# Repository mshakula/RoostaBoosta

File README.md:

# RoostaBoosta

Who doesn't need a good morning boost?
Return to your rich idyllic pastoral roots with RoostaBoosta™, the innovative, awesome, groundbreaking, fascinating, mind-boggling, stupendous IoT weather-predicting alarm clock!

Final project for Georgia Tech ECE4180.
Based on the newer [MbedOS 6](https://os.mbed.com/docs/mbed-os/v6.16/introduction/index.html) platform, this project incorporates networking, API calls, and audio-visual effects for an web-enabled alarm clock / weather prediction station.

## Building

Since the project is based on MbedOS 6, it strives to support the newer Mbed CLI 2, which among other things has [CMake support](https://os.mbed.com/docs/mbed-os/v6.16/build-tools/use.html#build-the-project-with-cmake-advanced).

In addition, this project also relies on [git submodules](https://git-scm.com/book/en/v2/Git-Tools-Submodules) for dependency management, since Mbed CLI tools for dependency management have been unreliable at best in the past.

### Requirements

- [Mbed CLI 2](https://os.mbed.com/docs/mbed-os/v6.16/build-tools/mbed-cli-2.html)
- [CMake](https://cmake.org/) >= v3.19
- [Supported Compiler](https://os.mbed.com/docs/mbed-os/v6.16/build-tools/index.html#:~:text=CLI%201%20page.-,compiler%20versions,-You%20can%20build)

### Process

Download the project files and all included dependencies:
```sh
git clone --recurse-submodules https://github.com/mshakula/RoostaBoosta.git
```

Alternatively, if the project is already checked out, do the following to update your dependencies:
```sh
git submodule update --init --recursive
```

To build, use standard CMake
```sh
cmake -S <project_dir> -B <output_directory>
cmake --build <output_directory> -t RoostaBoosta
```

### Online Compiler / Mbed Studio / Other compilers

We decided to use the Mbed CLI 2 / CMake as our main build tool since that seems to be the most actively supported solution for Mbed. Regardless, if another compilation solution is necessary, it may be possible to add add support with the following:

Create a symlink to `third_party/mbed-os` from the project root.
```sh
ln -s third_party/mbed-os mbed-os
```

Add a `mbed-os.lib` file that points to the checked out revision of mbed-os.
```sh
echo "https://github.com/ARMmbed/mbed-os.git#"$(cd third_party/mbed-os && git rev-parse HEAD) > mbed-os.lib
```

Note that this is not guaranteed to work if there are library conflicts and is not officially maintained.

## Branching 

All branches should be headed at `master`, which should be the stable build branch.

New features should be developed in parallel on `feature/[name]` branches.
Once a feature is complete, it can be merged into `master`.
Any features that depend on another should branch from the other one.
Features should only merge into their parent when they are certain that they work.

When merging back into `master` merge conflicts arise, they should be resolved in a local editor and tested before committing.
If any bug is retroactively found in `master`, a `bugfix/[name]` branch should be created and then merged back into it asap.

Master branch should have updated version numbers done in the top-level `CMakeLists.txt` file.
Feature branches can have the parent version number suffixed with the feature name.

## Style

Try to keep code legible and nice.
[Google C++ style guide](https://google.github.io/styleguide/cppguide.html) is good, with following exceptions:

- Use `.h` headers for C header files exclusively. Use `.hpp` for C++ headers.
- Avoid `/* */` style comments, prefer `//`.
- Use `/// \tag` style as opposed to `/** @tag` for doxygen parameter and function annotation.

A `.clang-format` is provided for all other formatting needs.
Please keep all checked-in code formatted by it.

## Hardware

The hardware used in this project is based on the hardware provided by the Georgia Tech ECE department.

Primary components used are:

- [mBed LPC1768](https://os.mbed.com/platforms/mbed-LPC1768/)
- [4D Systems uLCD-144-G2](https://www.sparkfun.com/products/11377)
- [HC-SRO4 Ultrasonic Sensor](https://www.sparkfun.com/products/15569)
- [Adafruit ESP8266 Breakout](https://www.adafruit.com/product/2471)
- [SparkFun microSD Breakout](https://www.sparkfun.com/products/544)
- [SparkFun RJ45 Ethernet Breakout](https://www.sparkfun.com/products/13021)
- [SparkFun TPA2005D1 Amp](https://www.sparkfun.com/products/11044)

Schematics and a breakout PCB are designed in [KiCAD](https://www.kicad.org/), which is free and open-source.

The hardware setup is currently as bare-bones as possible to simplify manual wiring.

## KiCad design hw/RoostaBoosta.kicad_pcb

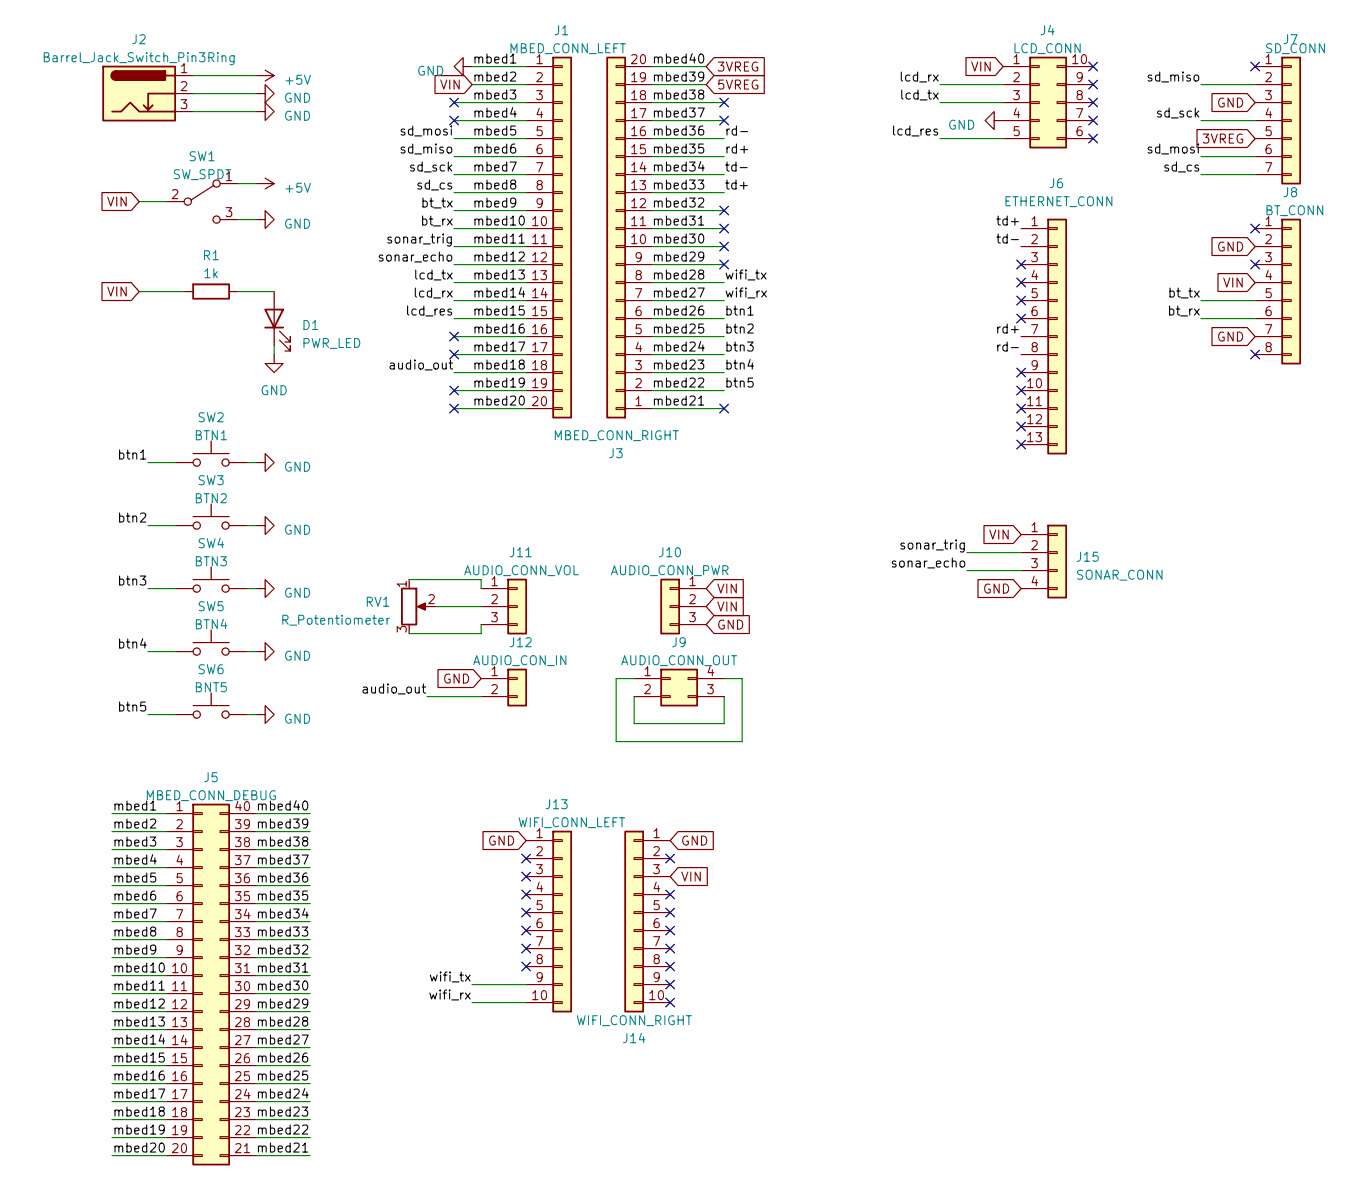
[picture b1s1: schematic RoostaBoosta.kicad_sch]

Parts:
D1: PWR_LED; LED_D1.8mm_W3.3mm_H2.4mm
J1: MBED_CONN_LEFT; PinHeader_1x20_P2.54mm_Vertical
J2: Barrel_Jack_Switch_Pin3Ring; BarrelJack_Horizontal
J3: MBED_CONN_RIGHT; PinHeader_1x20_P2.54mm_Vertical
J4: LCD_CONN; PinSocket_2x05_P2.54mm_Vertical
J5: MBED_CONN_DEBUG; PinHeader_2x20_P2.54mm_Vertical
J6: ETHERNET_CONN; PinSocket_1x13_P2.54mm_Vertical
J7: SD_CONN; PinSocket_1x07_P2.54mm_Vertical
J8: BT_CONN; PinSocket_1x08_P2.54mm_Vertical
J9: AUDIO_CONN_OUT; PinSocket_2x02_P2.54mm_Vertical
J10: AUDIO_CONN_PWR; PinSocket_1x03_P2.54mm_Vertical
J11: AUDIO_CONN_VOL; PinSocket_1x03_P2.54mm_Vertical
J12: AUDIO_CON_IN; PinSocket_1x02_P2.54mm_Vertical
J13: WIFI_CONN_LEFT; PinSocket_1x10_P2.54mm_Vertical
J14: WIFI_CONN_RIGHT; PinSocket_1x10_P2.54mm_Vertical
J15: SONAR_CONN; PinSocket_1x04_P2.54mm_Vertical
R1: 1k; R_Axial_DIN0207_L6.3mm_D2.5mm_P10.16mm_Horizontal
RV1: R_Potentiometer; Potentiometer_ACP_CA6-H2,5_Horizontal
SW1: SW_SPDT; SW_Slide_1P2T_CK_OS102011MS2Q
SW2: BTN1; SW_PUSH_6mm
SW3: BTN2; SW_PUSH_6mm
SW4: BTN3; SW_PUSH_6mm
SW5: BTN4; SW_PUSH_6mm
SW6: BNT5; SW_PUSH_6mm

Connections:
3VREG: J3.20, J5.40, J7.5
5VREG: J3.19, J5.39
+5V: J2.1, SW1.1 (A)
/audio_out: J1.18, J5.18, J12.2
/bt_rx: J1.10, J5.10, J8.6
/bt_tx: J1.9, J5.9, J8.5
/btn1: J3.6, J5.26, SW2.1
/btn2: J3.5, J5.25, SW3.1
/btn3: J3.4, J5.24, SW4.1
/btn4: J3.3, J5.23, SW5.1
/btn5: J3.2, J5.22, SW6.1
/lcd_res: J1.15, J4.5, J5.15
/lcd_rx: J1.14, J4.2, J5.14
/lcd_tx: J1.13, J4.3, J5.13
/mbed3: J1.3, J5.3
/mbed4: J1.4, J5.4
/mbed5: J1.5, J5.5, J7.6
/mbed6: J1.6, J5.6, J7.2
/mbed7: J1.7, J5.7, J7.4
/mbed8: J1.8, J5.8, J7.7
/mbed11: J1.11, J5.11, J15.2
/mbed12: J1.12, J5.12, J15.3
/mbed16: J1.16, J5.16
/mbed17: J1.17, J5.17
/mbed19: J1.19, J5.19
/mbed20: J1.20, J5.20
/mbed21: J3.1, J5.21
/mbed27: J3.7, J5.27, J13.10
/mbed28: J3.8, J5.28, J13.9
/mbed29: J3.9, J5.29
/mbed30: J3.10, J5.30
/mbed31: J3.11, J5.31
/mbed32: J3.12, J5.32
/mbed33: J3.13, J5.33, J6.1
/mbed34: J3.14, J5.34, J6.2
/mbed35: J3.15, J5.35, J6.7
/mbed36: J3.16, J5.36, J6.8
/mbed37: J3.17, J5.37
/mbed38: J3.18, J5.38
GND: D1.1 (K), J1.1, J2.2, J2.3, J4.4, J5.1, J7.3, J8.2, J8.7, J10.3, J12.1, J13.1, J14.1, J15.4, SW1.3 (C), SW2.2, SW3.2, SW4.2, SW5.2, SW6.2
unnamed: D1.2 (A), R1.1
unnamed: J9.1, J9.4
unnamed: J9.2, J9.3
unnamed: J11.1, RV1.1
unnamed: J11.2, RV1.2
unnamed: J11.3, RV1.3
VIN: J1.2, J4.1, J5.2, J8.4, J10.1, J10.2, J14.3, J15.1, R1.2, SW1.2 (B)

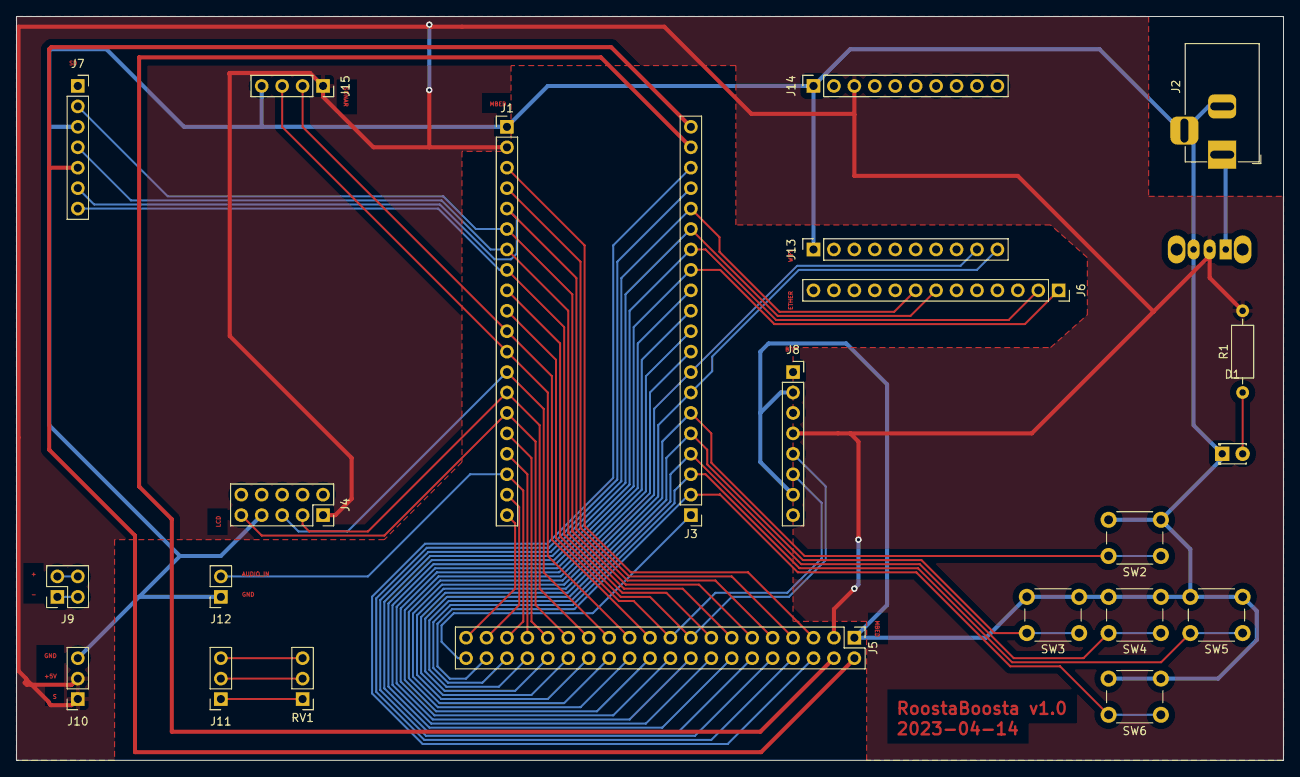
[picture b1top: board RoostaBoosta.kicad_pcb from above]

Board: 2 copper layers, 157.5 x 92.5 mm, 24 parts (1 on the bottom side), 47 nets.

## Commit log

2023-04-11 Added README.md
2023-04-12 Added initial project structure, with robust CMake + Mbed CLI 2 support.
2023-04-12 Added compile commands and bumped version to v0.0.1.
2023-04-12 feature/LCD-Patch:
    Added gitmodule for LCD library.
2023-04-13 Tests if LCD can print and clear
2023-04-16 hardware:
    Created v1.0 schematic and PCB design.
2023-04-18 Test for lcd working
2023-04-19 first working build of esp8266 lib. TODO: cleanup command send and implement http get requests
2023-04-20 hardware
    Added pinout header file for v1.0.
2023-04-22 Implemented display_weather fuction
2023-04-22 Added LCD display_weather function
2023-04-22 Formatting changes, fixed Mbed typo, minor other changes.
2023-04-22 Bumped LCD library version.
2023-04-22 Added DMA-based audio player and SD card support.
2023-04-22 Added music playing mutex. Changed music player to C-linkage.
2023-04-22 Added more interestring audio demo.
2023-04-22 Increased SD transfer frequency, fixed newline ordering.
2023-04-22 Fixed re-entrance issue, where playMusic() would stall when entering a second time.
2023-04-23 Ready for Testing
2023-04-23 refactor wificlient, use serial filestream to transmit data to esp8266
2023-04-24 first look at ethernet http requests
2023-04-24 Added audio_player files
2023-04-24 Fixed stereo/mono audio player issue. Fixed weather audio demo path generation. Changed weather_data* to a C structure. Formatting.
2023-04-25 update http request to use const char when appropriate
2023-04-25 wifi working interface with struct
2023-04-26 Formatting, and fixed weather string ownership. Made positive c++ changes.
2023-04-26 fixed "nintey zero" and added play_alarm()
2023-04-27 Merged #5 (audio_patch).
    Fixed "nintey zero" error.
    Fixed C-linkage previosly broken.
2023-04-27 Still non-functional. May rework to do async API, like I originally wanted to.
2023-04-27 Added skeletal HTTPClient implementation.
2023-04-28 Display_Time function added, accepts chrono::system_clock
2023-04-28 Display_Time function added, accepts chrono::system_clock, cleaner main
2023-04-28 addes Is_Snoozed, ready to be tested
2023-04-28 Sonar working, Is_Snoozed() returns true if someting is withing 10cm of sonar
2023-04-30 Added HTTP serialization.
2023-04-30 Fixed HTTPSerialization compile issues.
2023-04-30 Added serialization for HTTPRequest.
2023-05-01 Further iteration... compiles fully so far.
2023-05-01 Finished serialization... it works.
2023-05-01 Removed debug statements.
2023-05-02 Temporary async HTTP commit to save progress.
2023-05-02 Defined async request api.
2023-05-02 Some temporary improvements on WifiClient.
2023-05-02 minimum viable product release
2023-05-02 Remade WifiClient compiles...
